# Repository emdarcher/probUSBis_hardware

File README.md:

probUSBis Hardware
==================

Hardware files for probUSBis board.

This board is heavily inspired and based off of the [LittleWire](http://littlewire.cc/) and 
[DigiSpark](http://digistump.com/products/1) projects, with some little features of my own added to it.

The files are being made in KiCAD, but PDFs of the schematics will be made for releases.

Link to the [Hackaday Projects page](http://hackaday.io/project/3035) for this thing.

I have also made some code to run on this board in my [probUSBis_programs](https://github.com/emdarcher/probUSBis_programs) repository.

here is an image of the rev_a1 schamatic:

##WARNING!
* __rev_a1__ has a serious PCB error! The layout for the USB_A_MALE connector is flipped due to accidentally using a female layout. 
  - Solutions: 
    - if you still want a male USB plug on the board, you can solder it upside down, with pins sticking up into the bottom of the board.
    - Just don't use a male USB plug, and solder a suface mount female mini USB B jack on the top of the board in the designated location.

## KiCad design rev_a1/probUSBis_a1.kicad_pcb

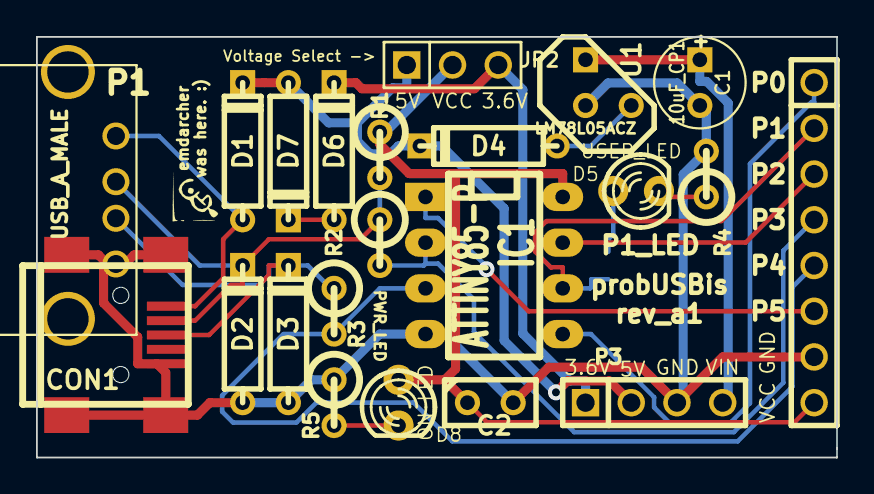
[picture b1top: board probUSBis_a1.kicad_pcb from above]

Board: 2 copper layers, 44.5 x 23.4 mm, 23 parts (1 on the bottom side), 19 nets.

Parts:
C1: 10uF_CP1; C1V5
C2: 100nF_C; C1
CON1: USB-MINI-B; USB_MINI_B
D1: Protect_DIODE; D3
D2, D3: 3.6V_ZENER; D3
D4: DIODE; D3
D5: USER_LED; LED-3MM
D6, D7: Si_DIODE; D3
D8: ON_LED; LED-3MM
IC1: ATTINY85-P; DIP-8__300_ELL
JP1: JUMPER; SM0603
JP2: JUMPER3; PIN_ARRAY_3X1
P1: USB_A_MALE; USB_A
P2: CONN_8; pin8x1
P3: CONN_4; pin4x1
R1: 1.5K_R; R1
R2, R3: 68R; R1
R4, R5: 1K_R; R1
U1: LM78L05ACZ; TO92

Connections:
+3.3V: D6.2, JP2.3, P3.1
+5V: D1.2, D4.2, D7.1, JP2.1, P3.2
GND: C1.2, C2.2, CON1.5, CON1.6, CON1.7, CON1.8, CON1.9, D2.1, D3.1, IC1.4, P1.4, P2.7, P3.3, R4.2, R5.1, U1.2
unnamed: IC1.1, P2.6
unnamed: CON1.1, D1.1, P1.1
unnamed: IC1.5, P2.1
unnamed: IC1.6, JP1.1, P2.2
unnamed: IC1.7, P2.3
unnamed: D8.2, R5.2
unnamed: D5.1, JP1.2
unnamed: D5.2, R4.1
unnamed: D6.1, D7.2
unnamed: IC1.3, P2.5, R3.2
unnamed: D4.1, U1.3
unnamed: CON1.3, D3.2, P1.3, R3.1
unnamed: CON1.2, D2.2, P1.2, R1.2, R2.1
unnamed: IC1.2, P2.4, R2.2
VCC: C2.1, D8.1, IC1.8, JP2.2, P2.8, R1.1
VIN: C1.1, P3.4, U1.1

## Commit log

2014-09-02 first commit, started kicad project and made readme
2014-09-02 added the OHL license, may change to a creative commons one later
2014-09-03 made schematic, mostly done with it
2014-09-03 moved a1 files to a separate folder
2014-09-03 added some more info to the README
2014-09-03 added jumper for user led on PB1
2014-09-03 made netlist
2014-09-03 did first setup of footprints for parts
2014-09-03 made a README file in rev_a1 folder for documentation
2014-09-04 did some random pcb stuff
2014-09-05 made some changes to pcb, added cut edge
2014-09-05 made dsn, also making pin labels
2014-09-05 editing pcb layout, trying to compress more
2014-09-05 moving usb around, fiddling with the pcb
2014-09-05 moved stuff around, fixed 5v ref layout
2014-09-15 did some routing with freerouter
2014-09-16 adding more info to back silkscreen
2014-09-16 made logo thing
2014-09-16 messing with bitmap to component stuff
2014-09-16 added logo on back of pcb, flipped
2014-09-16 a delete
2014-09-16 added oshw logo to board
2014-09-16 added a ground fill
2014-09-16 made gerber and drill files for production
2014-09-16 silkscreen stuff, editing part label locations
2014-09-16 saved pcb, redid the gerber files. did some jixes to silkscreen names
2014-09-17 generating files
2014-09-18 put stuff in a folder to make zip for OSHPark
2014-09-25 added HaDP link to readme
2014-09-28 made some holes bigger, and made new pin modules to do so.
2014-09-28 re-did the gerbers and drill files
2014-10-03 fixing some stuff, making schematic pdf
2014-10-08 added image
2014-10-08 quick fix to readme
2014-10-08 added link to probUSBis_programs in the README
2014-10-08 line fix in readme
2014-12-15 readme warning stuff
